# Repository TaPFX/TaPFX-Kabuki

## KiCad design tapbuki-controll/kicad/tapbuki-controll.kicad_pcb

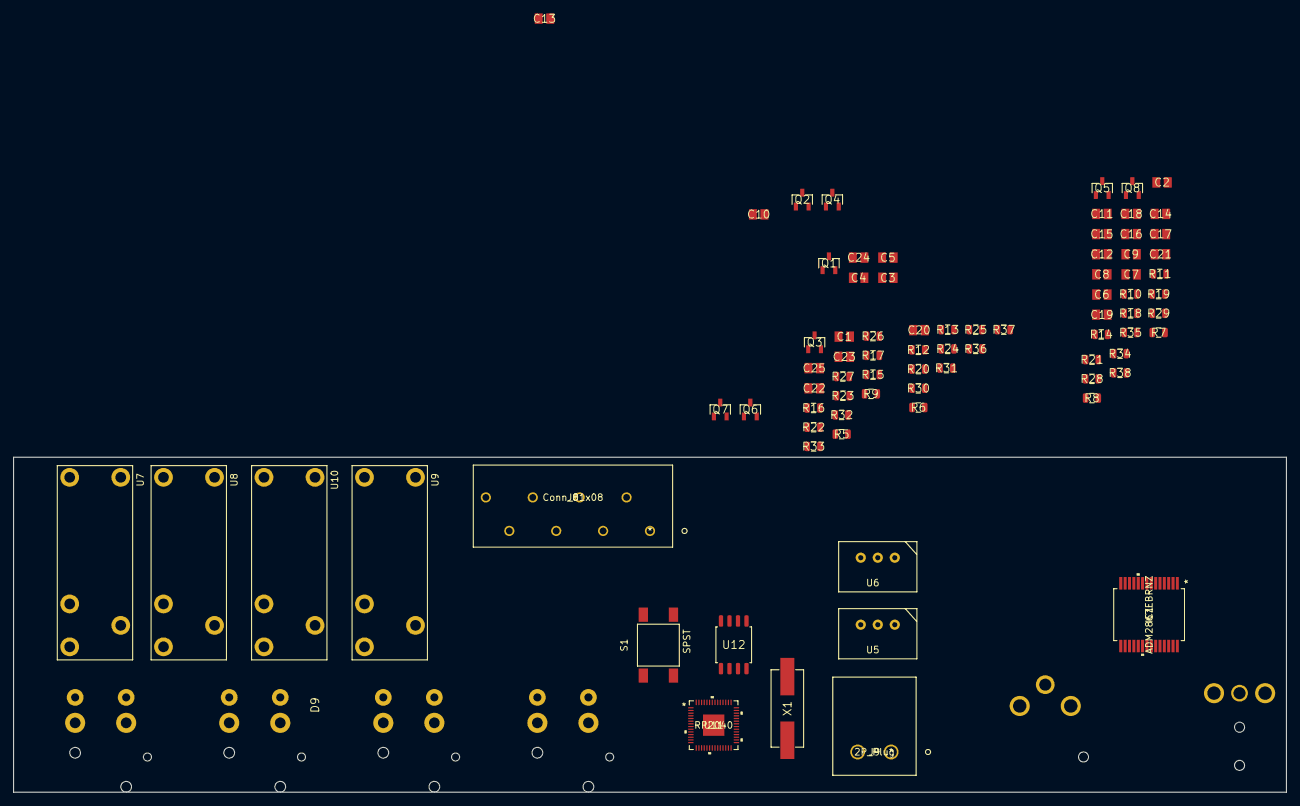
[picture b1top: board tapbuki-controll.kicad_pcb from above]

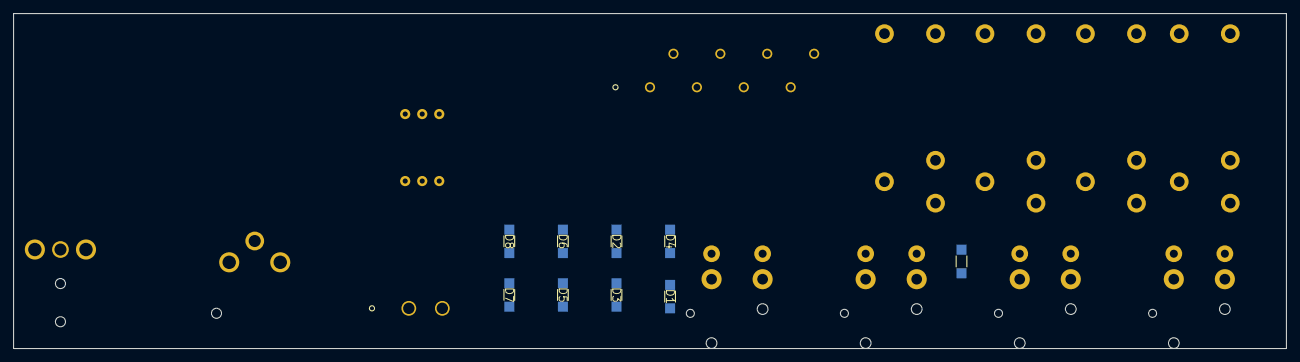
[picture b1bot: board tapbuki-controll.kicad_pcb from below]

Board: 2 copper layers, 190.0 x 50.0 mm, 95 parts (9 on the bottom side), 58 nets, no tracks yet.

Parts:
C1, C2, C3, C4, C6, C7, C8, C9, C10, C11, C12, C14, C19, C20, C21, C22, C23, C24: 100nF; CAP0805
C5, C13, C15, C16, C17, C18, C25: 10uF; CAP0805
D1, D2, D3, D4, D5, D6, D7, D8, D9: LED; led1206_bivar_SM
IC1: ADM2867EBRNZ
J1, J2, J3, J4: NC4FAHL1; NC4FAH0
J5: NC3FAHL1
J6: NC3MAHR
J8: Conn_01x08; 250-208
J9: 2P_Plug; 2092-1402
Q1, Q2, Q3, Q4, Q5, Q6, Q7, Q8: 2N2222; SOT23-3P95_MMBZxxxALT1G
R5: 1; RES0805
R6, R7, R8, R9, R10, R11, R12, R13, R14, R15, R16, R17, R18, R19, R28, R29, R30, R31, R32, R33, R34, R35: 220; RES0805
R20, R21, R22, R23, R24, R25, R26, R27, R36: 320; RES0805
R37, R38: 1k; RES0805
S1: SPST; te-microswitch-smd
U5, U6: TSR1-2450; TSRN_1_2450
U7, U8, U9, U10: RelaySP; JS-05
U11: RP2040
U12: W25Q128JVS; SOIC8P_w25q128
X1: XTAL; XTAL1140X470X420D1270L390X60

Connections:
+3V3: C10.2, C17.1, C19.1, C20.1, C21.1, C22.1, C23.1, C24.1, C25.1, IC1.7, R20.1, R21.1, R22.1, R23.1, R24.1, R25.1, R26.1, R27.1, R36.1, U6.3, U11.1, U11.10, U11.22, U11.33, U11.42, U11.43, U11.44, U11.48, U11.49, U12.8
+5VD: C1.1, C2.1, C3.1, C4.1, C5.1, C14.1, C15.1, IC1.4, J8.2, J8.4, J8.6, J8.8, J9.2, R5.2, R12.2, R13.2, R14.2, R15.2, U5.1, U5.3, U6.1, U7.5, U8.5, U9.5, U10.5
/CH1-RDY: Q5.3, U11.3
/CH1-RELAY: R16.2, U11.15
/CH2-RDY: Q6.3, U11.5
/CH2-RELAY: R17.2, U11.16
/CH3-RDY: Q7.3, U11.7
/CH3-RELAY: R18.2, U11.17
/CH4-RDY: Q8.3, U11.9
/CH4-RELAY: R19.2, U11.18
/GPIO10: IC1.11, U11.13
/USB-D+: R6.2, U11.47
/USB-D-: R7.2, U11.46
GND: C1.2, C2.2, C3.2, C4.2, C6.2, C7.2, C8.2, C9.2, C10.1, C16.1, C17.2, C18.1, C19.2, C20.2, C21.2, C22.2, C23.2, C24.2, C25.2, IC1.15, IC1.16, IC1.21, IC1.22, J1.4, J2.4, J3.4, J4.4, J9.1, Q1.1, Q2.1, Q3.1, Q4.1, Q5.1, Q6.1, Q7.1, Q8.1, R32.1, R33.1, R34.1, R35.1, S1.1, U5.2, U6.2, U11.57, U12.4
GND_DMX: C5.2, C11.2, C12.2, C13.2, C14.2, C15.2, IC1.24, IC1.26, IC1.28, J5.3, J6.3
unnamed: C6.1, U11.38
unnamed: C7.1, U11.39
unnamed: C8.1, U11.40
unnamed: C9.1, U11.41
unnamed: C11.1, IC1.25, IC1.27
unnamed: C12.1, C13.1, IC1.23
unnamed: C16.2, R37.1, X1.2
unnamed: C18.2, U11.20, X1.1
unnamed: IC1.19, J5.1, J6.1
unnamed: IC1.20, J5.2, J6.2
unnamed: J1.3, R8.1
unnamed: J2.3, R9.1
unnamed: J3.3, R10.1
unnamed: J4.3, R11.1
unnamed: J8.1, R8.2, R28.1, U7.4
unnamed: J8.3, R9.2, R29.1, U8.4
unnamed: J8.5, R10.2, R30.1, U9.4
unnamed: J8.7, R11.2, R31.1, U10.4
unnamed: Q1.2, R16.1
unnamed: Q1.3, U7.1
unnamed: Q2.2, R17.1
unnamed: Q2.3, U8.1
unnamed: Q3.2, R18.1
unnamed: Q3.3, U9.1
unnamed: Q4.2, R19.1
unnamed: Q4.3, U10.1
unnamed: Q5.2, R28.2, R32.2
unnamed: Q6.2, R29.2, R33.2
unnamed: Q7.2, R30.2, R34.2
unnamed: Q8.2, R31.2, R35.2
unnamed: R12.1, U7.2
unnamed: R13.1, U8.2
unnamed: R14.1, U9.2
unnamed: R15.1, U10.2
unnamed: R37.2, U11.21
unnamed: R38.1, U11.56, U12.1
unnamed: R38.2, S1.2
unnamed: U11.23, U11.45, U11.50
unnamed: U11.51, U12.7
unnamed: U11.52, U12.6
unnamed: U11.53, U12.5
unnamed: U11.54, U12.2
unnamed: U11.55, U12.3

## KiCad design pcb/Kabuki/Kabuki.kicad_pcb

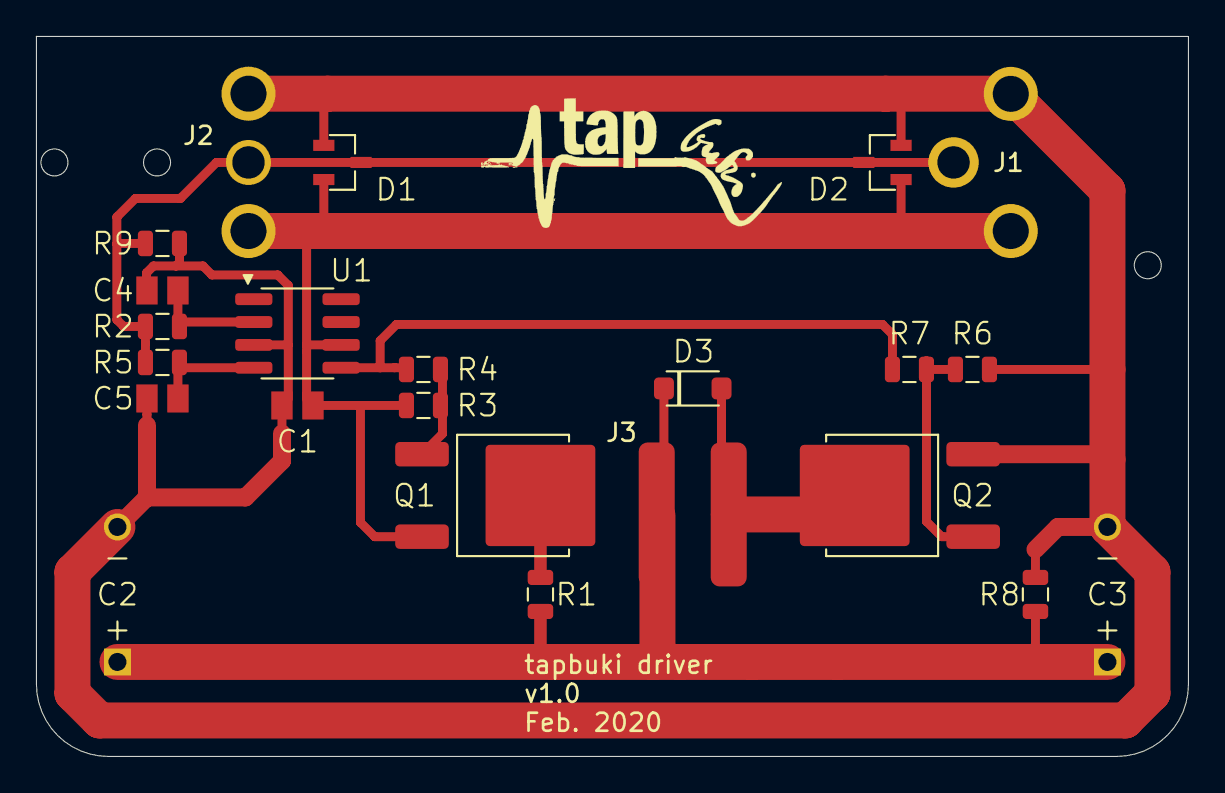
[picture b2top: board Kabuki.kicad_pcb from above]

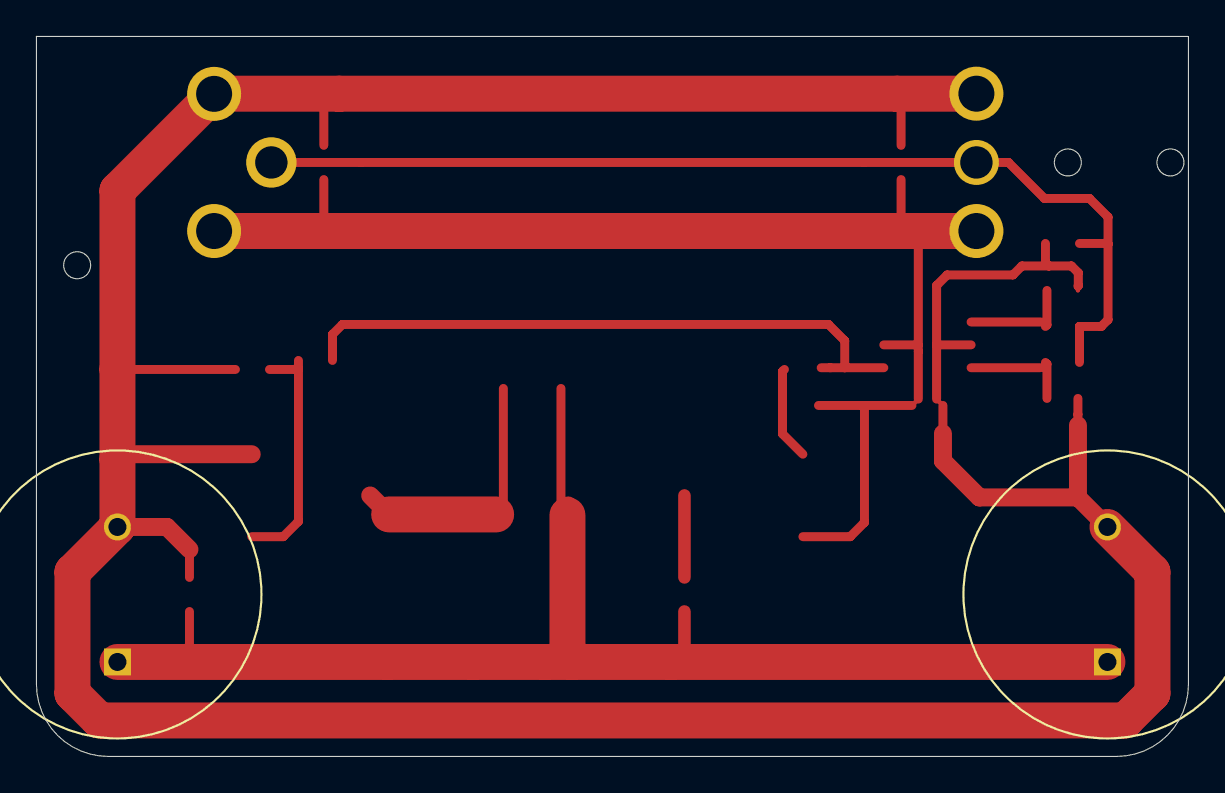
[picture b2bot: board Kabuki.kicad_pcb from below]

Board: 2 copper layers, 64.0 x 40.0 mm, 23 parts (4 on the bottom side), 12 nets.

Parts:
C1, C4, C5: capcer0805; CAP0805
C2, C3: 4700u; CAPPRD750W80D1600H3200
D1, D2: MMBZxxxALT1G; SOT23-3P95_MMBZxxxALT1G
D3: SS1FH6HM3; SODFL_SS1FH6
J1: NC3FAHL1
J2: NC3MAHR
J3: Solenoide
Q1: FQD17P06; DPAK4P229_FQD17P06
Q2: FQD18N20V2TM; DPAK4P229_FQD18N20V2
R1: 220; RES0805
R2, R3, R5, R6: 1k; RES0805
R4, R7: 470; RES0805
R8, R9: 10k; RES0805
U1: IX4428N; SOIC8P127_IX44XX

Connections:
+5VD: C1.1, D1.2, D2.1, J1.3, J2.3, Q1.3, R3.1, U1.6
GND: C1.2, C2.2, C3.2, C4.1, C5.1, D1.1, D2.2, J1.1, J2.1, Q2.2, R6.1, R8.2, R9.2, U1.3
unnamed: C2.1, C3.1, D3.C, J3.1, R1.2, R8.1
unnamed: C4.2, R2.1, U1.2
unnamed: C5.2, R5.1, U1.4
unnamed: D1.3, D2.3, J1.2, J2.2, R2.2, R5.2, R9.1
unnamed: D3.A, J3.2, Q2.3
unnamed: Q1.1, R3.2, R4.2
unnamed: Q1.4, R1.1
unnamed: Q2.1, R6.2, R7.1
unnamed: R4.1, R7.2, U1.5
unnamed: U1.1, U1.8

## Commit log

2020-01-24 add CAD
2020-01-26 update design
2020-01-26 update hole
2020-01-26 add new magnet
2020-01-29 add v2
2020-02-01 add logos
2020-02-04 add sim add PMOS
2020-02-04 update and order
2020-02-11 add tapbuki controll
2021-05-07 add PCB CAD
2021-05-07 restructure CAD
2021-05-07 add typC

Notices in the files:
parts and their libraries:
Copyright 2021 Accelerated Designs. All rights reserved.
